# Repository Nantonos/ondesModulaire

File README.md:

ondesModulaire
==============

Eurorack analog synth implementation of ondes Martenot. This uses a
mixture of commercial and DIY modules. The controllers and the speakers
are all DIY. See [the patch](Patch.md).

This repository documents the DIY modules that I am making specific to
this project (as opposed to kits or designs made by others).

- [Precision rectifier](precision%20rectifier/readme.md)
- [Dual Comparator](dual%20comparator/)
- [ondesMix](wavemix/)
- [Offsets](offsets/)
- [Transpositeurs](transpositeurs/)

It is also documenting the controllers I am making, and the speakers.

The keyboard controller was started, was partly working, and was then
abandoned as the keybed was too heavy for the keyboard shake vibrato function.
The keys were also regular sized rather than the smaller OM style.
Documentation at http://nantonos.github.io/ondesModulaire/keyboard/docs/

Lastly, this repository houses resources (screenshots, recordings, notes)
related to ongoing experiments to find the best emulation.

[Planned state of the modules](http://www.modulargrid.net/e/racks/view/30175) is available on Modular Grid and is updated
as experiments proceed.

The [actual current state](http://www.modulargrid.net/e/racks/view/61770) is also available and is updated as modules are purchased, built, or designed and built,
respectively.

A [discussion thread on Modwiggler forum](http://www.muffwiggler.com/forum/viewtopic.php?p=1261346) is the main place where this and related
projects are discussed

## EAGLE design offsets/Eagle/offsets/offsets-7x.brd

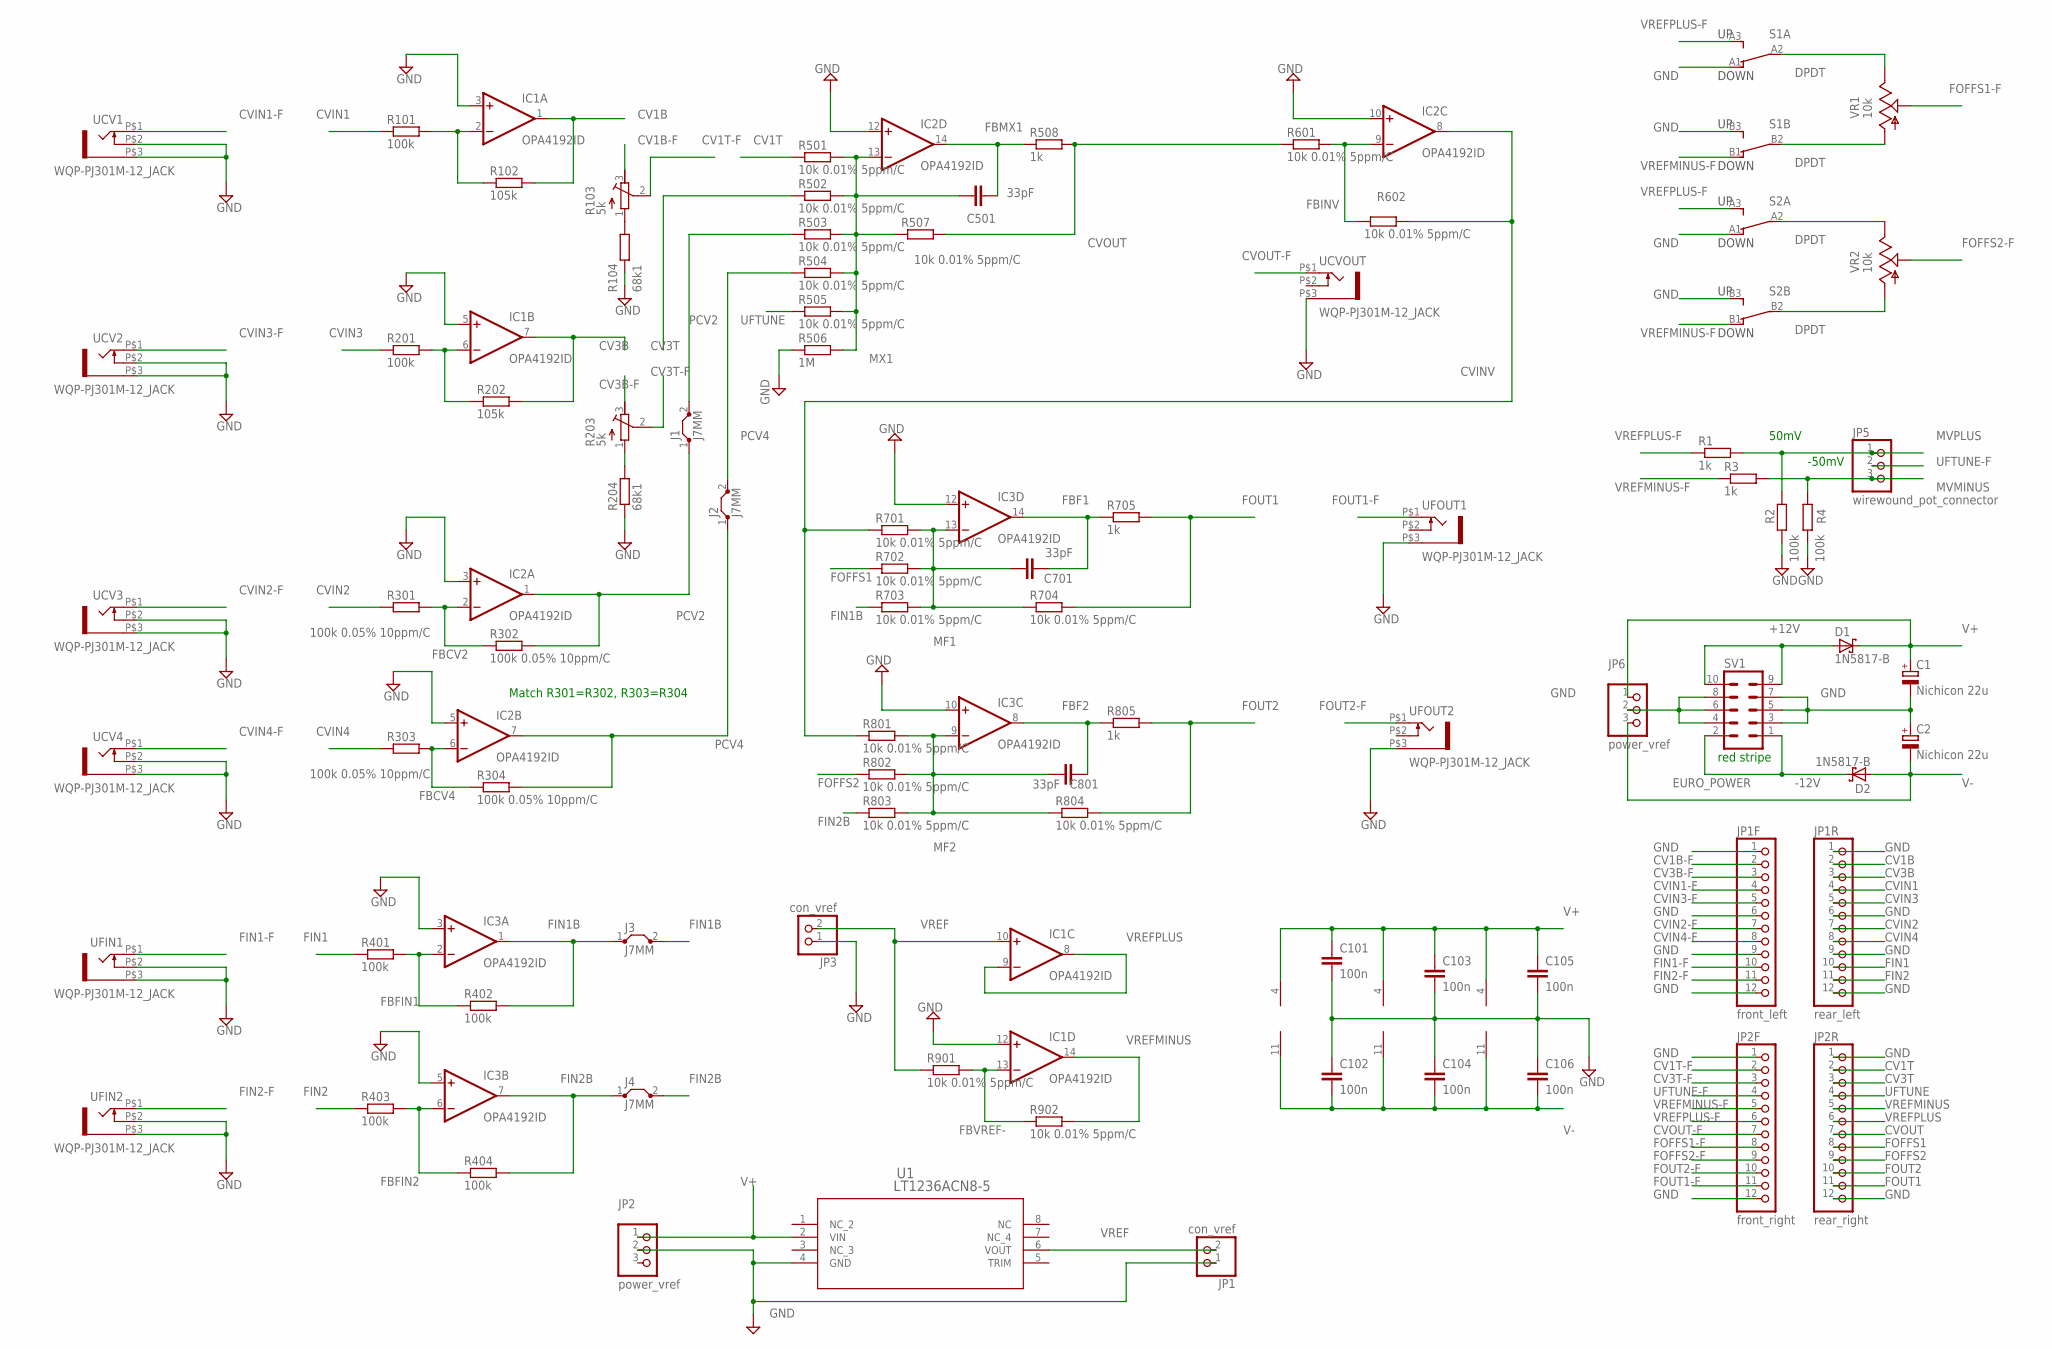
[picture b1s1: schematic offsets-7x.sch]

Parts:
C1, C2: Nichicon 22u; E2,5-5
C101, C102, C103, C104, C105, C106: 100n; C1206
C501, C701, C801: 33pF; C0805K
D1, D2: 1N5817-B; DO41-7.6
IC1, IC2, IC3: OPA4192ID; SO14
J1, J2, J3, J4: J7MM; 07
JP1, JP3: con_vref; 1X02
JP1F: front_left; 1X12
JP1R: rear_left; 1X12
JP2, JP6: power_vref; 1X03
JP2F: front_right; 1X12
JP2R: rear_right; 1X12
JP5: wirewound_pot_connector; 1X03
R1, R3, R508, R705, R805: 1k; R0805W
R2, R4, R101, R201, R401, R402, R403, R404: 100k; R0805W
R102, R202: 105k; R0805W
R103, R203: 5k; RTRIM3296W
R104, R204: 68k1; R0805W
R301, R302, R303, R304: 100k 0.05% 10ppm/C; R0805W
R501, R502, R503, R504, R505, R507, R601, R602, R701, R702, R703, R704, R801, R802, R803, R804, R901, R902: 10k 0.01% 5ppm/C; R0805W
R506: 1M; R0805W
S1, S2: DPDT; DPDT-VERTICAL-TOP-SUBMINI-MULTICOMP
SV1: EURO_POWER; EURO_POWER_HEADER
U1: LT1236ACN8-5; PDIP-8_N
UCV1, UCV2, UCV3, UCV4: WQP-PJ301M-12_JACK
UCVOUT: WQP-PJ301M-12_JACK
UFIN1, UFIN2: WQP-PJ301M-12_JACK
UFOUT1, UFOUT2: WQP-PJ301M-12_JACK
VR1, VR2: 10k; 9MM_SNAP-IN_POT

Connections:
+12V: D1.A, SV1.9, SV1.10
-12V: D2.C, SV1.1, SV1.2
CV1B: IC1.1 (OUT), JP1R.2, R102.2
CV1B-F: JP1F.2, R103.3 (E)
CV1T: JP2R.2, R501.1
CV1T-F: JP2F.2, R103.2 (S)
CV3B: IC1.7 (OUT), JP1R.3, R202.2
CV3B-F: JP1F.3, R203.3 (E)
CV3T: JP2R.3, R502.1
CV3T-F: JP2F.3, R203.2 (S)
CVIN1: JP1R.4, R101.1
CVIN1-F: JP1F.4, UCV1.P$1 (2)
CVIN2: JP1R.7, R301.1
CVIN2-F: JP1F.7, UCV3.P$1 (2)
CVIN3: JP1R.5, R201.1
CVIN3-F: JP1F.5, UCV2.P$1 (2)
CVIN4: JP1R.8, R303.1
CVIN4-F: JP1F.8, UCV4.P$1 (2)
CVINV: IC2.8 (OUT), R602.2, R701.1, R801.1
CVOUT: JP2R.7, R507.2, R508.2, R601.1
CVOUT-F: JP2F.7, UCVOUT.P$1 (2)
FBCV2: IC2.2 (-IN), R301.2, R302.1
FBCV4: IC2.6 (-IN), R303.2, R304.1
FBF1: C701.2, IC3.14 (OUT), R705.1
FBF2: C801.2, IC3.8 (OUT), R805.1
FBFIN1: IC3.2 (-IN), R401.2, R402.1
FBFIN2: IC3.6 (-IN), R403.2, R404.1
FBINV: IC2.9 (-IN), R601.2, R602.1
FBMX1: C501.2, IC2.14 (OUT), R508.1
FBVREF-: IC1.13 (-IN), R901.2, R902.1
FIN1: JP1R.10, R401.1
FIN1-F: JP1F.10, UFIN1.P$1 (2)
FIN1B: IC3.1 (OUT), J3.1, J3.2, R402.2, R703.1
FIN2: JP1R.11, R403.1
FIN2-F: JP1F.11, UFIN2.P$1 (2)
FIN2B: IC3.7 (OUT), J4.1, J4.2, R404.2, R803.1
FOFFS1: JP2R.8, R702.1
FOFFS1-F: JP2F.8, VR1.2 (S)
FOFFS2: JP2R.9, R802.1
FOFFS2-F: JP2F.9, VR2.2 (S)
FOUT1: JP2R.11, R704.2, R705.2
FOUT1-F: JP2F.11, UFOUT1.P$1 (2)
FOUT2: JP2R.10, R804.2, R805.2
FOUT2-F: JP2F.10, UFOUT2.P$1 (2)
GND: C1.-, C2.+, C101.2, C102.1, C103.2, C104.1, C105.2, C106.1, IC1.3 (+IN), IC1.5 (+IN), IC1.12 (+IN), IC2.3 (+IN), IC2.5 (+IN), IC2.10 (+IN), IC2.12 (+IN), IC3.3 (+IN), IC3.5 (+IN), IC3.10 (+IN), IC3.12 (+IN), JP1.1, JP1F.1, JP1F.6, JP1F.9, JP1F.12, JP1R.1, JP1R.6, JP1R.9, JP1R.12, JP2.2, JP2F.1, JP2F.12, JP2R.1, JP2R.12, JP3.1, JP6.2, R2.1, R4.1, R104.1, R204.1, R506.1, S1.A1 (1), S1.B3 (3), S2.A1 (1), S2.B3 (3), SV1.3, SV1.4, SV1.5, SV1.6, SV1.7, SV1.8, U1.4 (GND), UCV1.P$2 (3), UCV1.P$3 (1), UCV2.P$2 (3), UCV2.P$3 (1), UCV3.P$2 (3), UCV3.P$3 (1), UCV4.P$2 (3), UCV4.P$3 (1), UCVOUT.P$3 (1), UFIN1.P$2 (3), UFIN1.P$3 (1), UFIN2.P$2 (3), UFIN2.P$3 (1), UFOUT1.P$3 (1), UFOUT2.P$3 (1)
MF1: C701.1, IC3.13 (-IN), R701.2, R702.2, R703.2, R704.1
MF2: C801.1, IC3.9 (-IN), R801.2, R802.2, R803.2, R804.1
MVMINUS: JP5.3, R3.2, R4.2
MVPLUS: JP5.1, R1.2, R2.2
MX1: C501.1, IC2.13 (-IN), R501.2, R502.2, R503.2, R504.2, R505.2, R506.2, R507.1
unnamed: IC1.2 (-IN), R101.2, R102.1
unnamed: IC1.6 (-IN), R201.2, R202.1
unnamed: R103.1 (A), R104.2
unnamed: R203.1 (A), R204.2
unnamed: S1.A2 (2), VR1.3 (E)
unnamed: S1.B2 (2), VR1.1 (A)
unnamed: S2.A2 (2), VR2.3 (E)
unnamed: S2.B2 (2), VR2.1 (A)
PCV2: IC2.1 (OUT), J1.1, J1.2, R302.2, R503.1
PCV4: IC2.7 (OUT), J2.1, J2.2, R304.2, R504.1
UFTUNE: JP2R.4, R505.1
UFTUNE-F: JP2F.4, JP5.2
V+: C1.+, C101.1, C103.1, C105.1, D1.C, IC1.4 (V+), IC2.4 (V+), IC3.4 (V+), JP2.1, JP6.1, U1.2 (VIN)
V-: C2.-, C102.2, C104.2, C106.2, D2.A, IC1.11 (V-), IC2.11 (V-), IC3.11 (V-), JP6.3
VREF: IC1.10 (+IN), JP1.2, JP3.2, R901.1, U1.6 (VOUT)
VREFMINUS: IC1.14 (OUT), JP2R.5, R902.2
VREFMINUS-F: JP2F.5, R3.1, S1.B1 (1), S2.B1 (1)
VREFPLUS: IC1.8 (OUT), IC1.9 (-IN), JP2R.6
VREFPLUS-F: JP2F.6, R1.1, S1.A3 (3), S2.A3 (3)

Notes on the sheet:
50mV
-50mV
red stripe
Match R301=R302, R303=R304

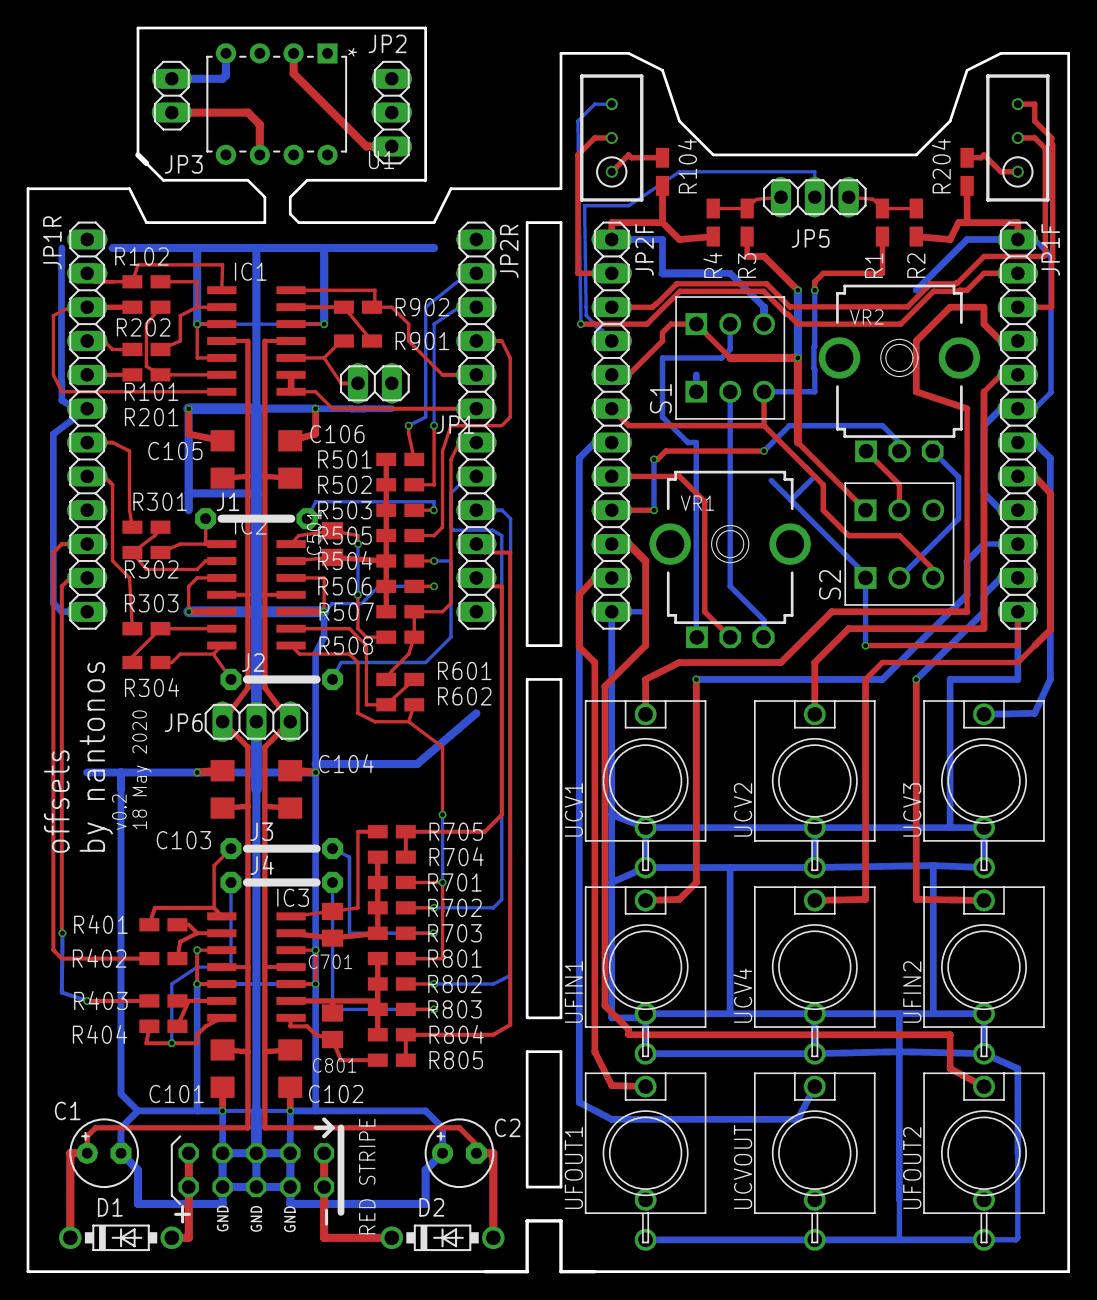
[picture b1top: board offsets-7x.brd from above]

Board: 2 copper layers, 77.9 x 93.2 mm, 86 parts (0 on the bottom side), 69 nets.

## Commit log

2024-06-18 Add Eagle files
2024-06-18 move Eagle files
2024-06-19 exported as legacy Eagle 7.x format
2024-06-19 Rename readme to readme.md
